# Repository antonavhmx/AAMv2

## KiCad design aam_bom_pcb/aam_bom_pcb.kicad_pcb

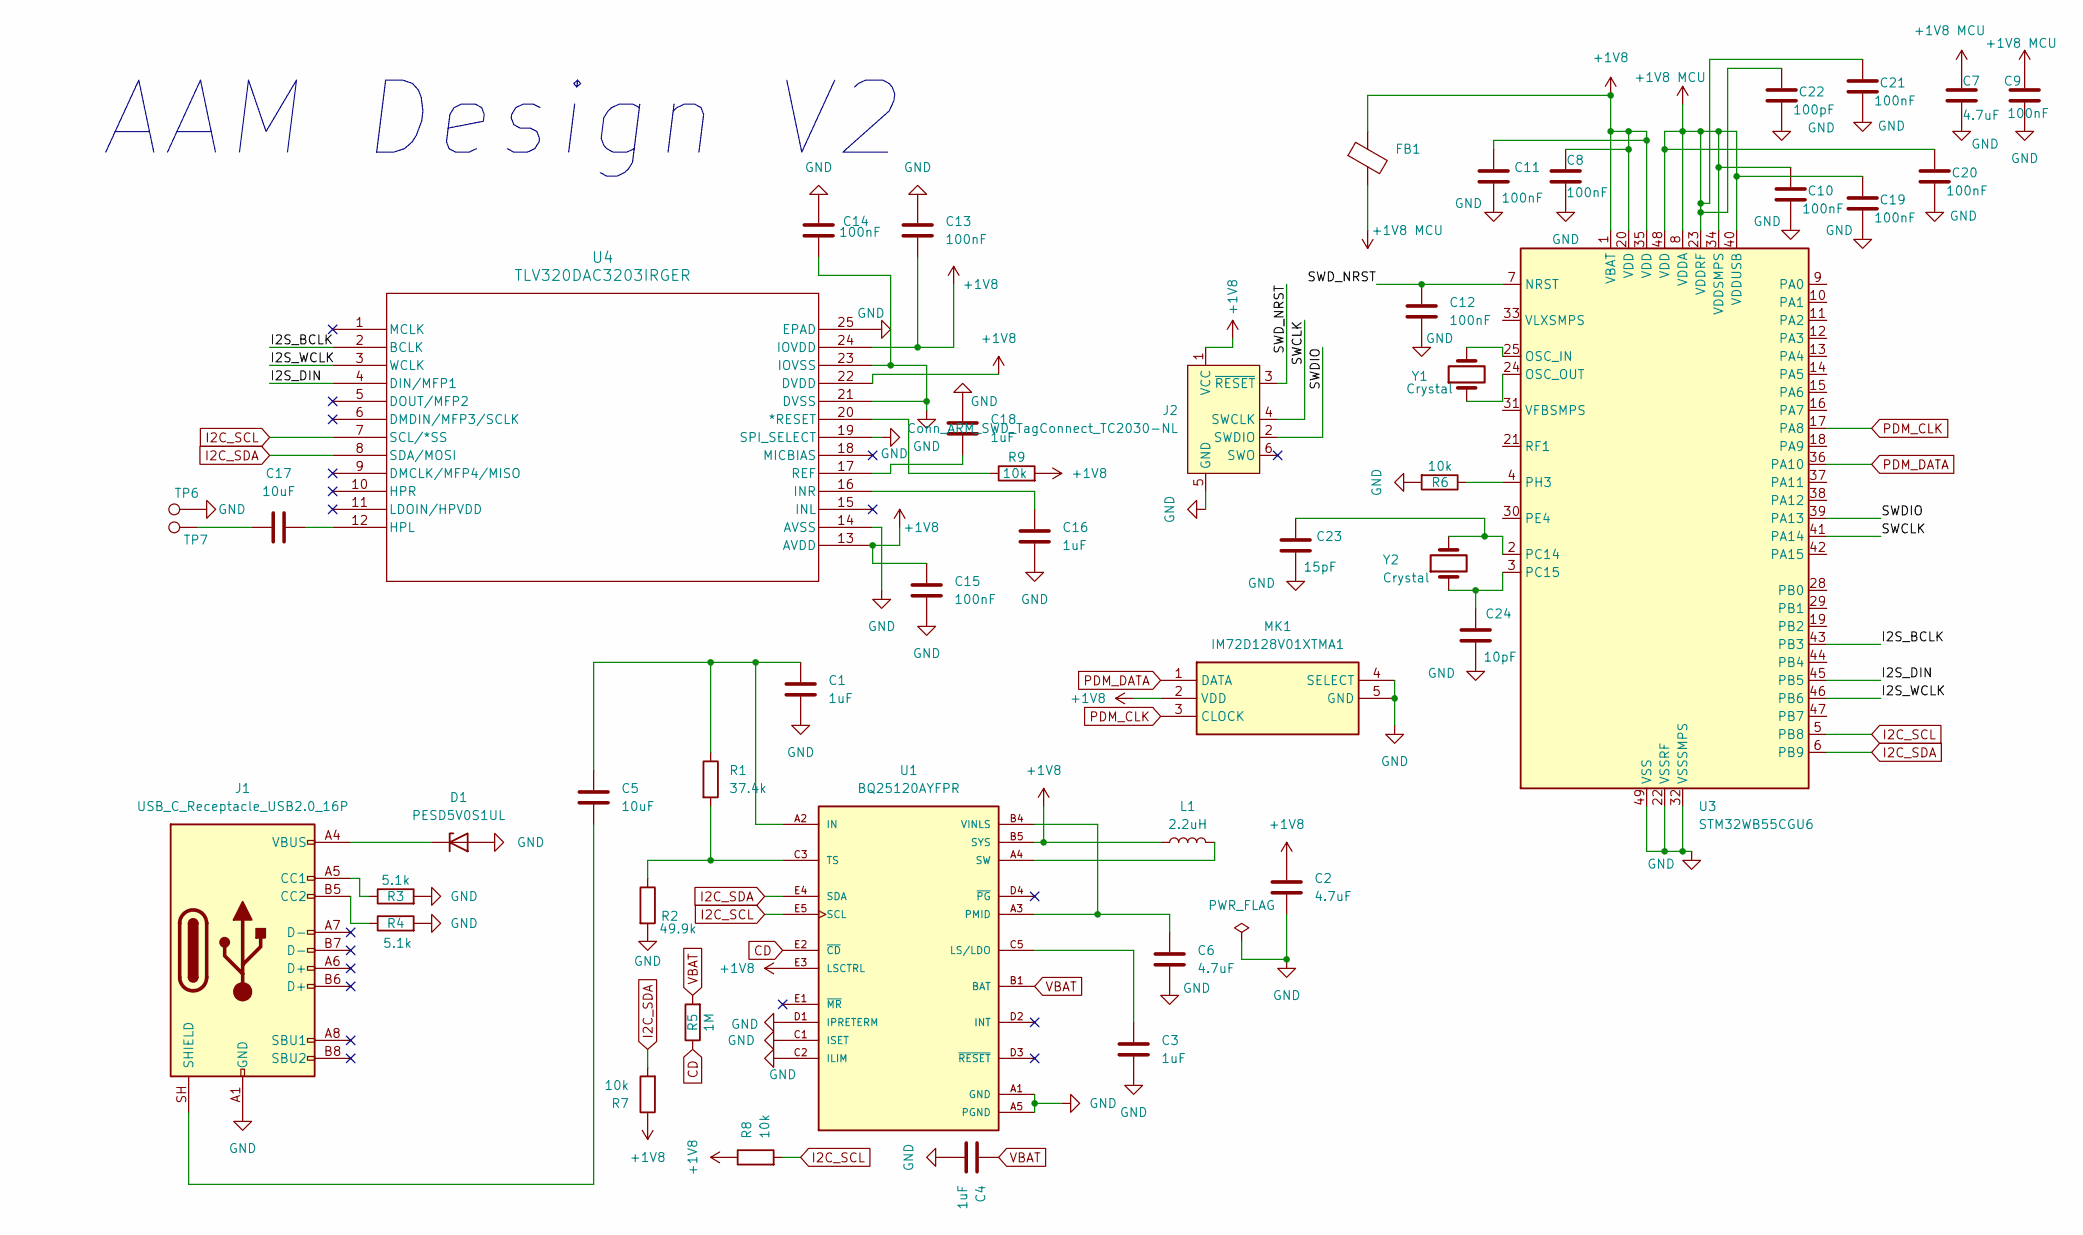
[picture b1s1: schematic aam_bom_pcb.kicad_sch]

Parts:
C1, C3, C4, C16, C18: 1uF; C_0402_1005Metric; LCSC C52923
C2, C6, C7: 4.7uF; C_0402_1005Metric; LCSC C23733
C5, C17: 10uF; C_0402_1005Metric; LCSC C307415
C8, C9, C10, C11, C12, C13, C14, C15, C19, C20, C21: 100nF; C_0402_1005Metric; LCSC C307331
C22: 100pF; C_0402_1005Metric; LCSC C307331
C23: 15pF; C_0402_1005Metric; LCSC C307331
C24: 10pF; C_0402_1005Metric; LCSC C307331
D1: PESD5V0S1UL; D_SOD-882; LCSC C552570
FB1: 600R@100MHz; L_0402_1005Metric; LCSC C76884
J1: USB_C_Receptacle_USB2.0_16P; USB_C_Receptacle_HCTL_HC-TYPE-C-16P-01A; LCSC C2894897
J2: Conn_ARM_SWD_TagConnect_TC2030-NL; Tag-Connect_TC2030-IDC-NL_2x03_P1.27mm_Vertical
L1: 2.2uH; L_1008_2520Metric; LCSC C222790
MK1: IM72D128V01XTMA1; Mouser Part Number 726-IM72D128V01XTMA1
R1: 37.4k; R_0402_1005Metric; LCSC C185422
R2: 49.9k; R_0402_1005Metric; LCSC C137969
R3, R4: 5.1k; R_0402_1005Metric; LCSC C105872
R5: 1M; R_0402_1005Metric; LCSC C138033
R6, R7, R8, R9: 10k; R_0402_1005Metric; LCSC C60490
TP6, TP7: TestPoint; TestPoint_Pad_1.5x1.5mm
U1: BQ25120AYFPR; IC_BQ25120AYFPR; PARTREV A; LCSC C2866577
U3: STM32WB55CGU6; QFN-48-1EP_7x7mm_P0.5mm_EP5.6x5.6mm; LCSC C404023
U4: TLV320DAC3203IRGER; RGE24_2P7X2P7_TEX; LCSC C473906
Y1: Crystal; Crystal_SMD_2016-4Pin_2.0x1.6mm; LCSC C9009
Y2: Crystal; Crystal_SMD_2012-2Pin_2.0x1.2mm; LCSC C32346

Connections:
+1V8: C2.1, C8.1, C11.1, C13.2, C15.1, FB1.1, J2.1 (VCC), L1.1, MK1.2 (VDD), R7.1, R8.1, R9.2, U1.B5 (SYS), U1.E3 (LSCTRL), U3.1 (VBAT), U3.20 (VDD), U3.35 (VDD), U4.13 (AVDD), U4.22 (DVDD), U4.24 (IOVDD)
+1V8 MCU: C7.1, C9.1, C10.1, C19.1, C20.1, C21.1, C22.1, FB1.2, U3.8 (VDDA), U3.23 (VDDRF), U3.34 (VDDSMPS), U3.40 (VDDUSB), U3.48 (VDD)
/I2S_BCLK: U3.43 (PB3), U4.2 (BCLK)
/I2S_DIN: U3.45 (PB5), U4.4 (DIN/MFP1)
/I2S_WCLK: U3.46 (PB6), U4.3 (WCLK)
/SWCLK: J2.4 (SWCLK), U3.41 (PA14)
/SWDIO: J2.2 (SWDIO), U3.39 (PA13)
/SWD_NRST: C12.1, J2.3 (~RESET), U3.7 (NRST)
CD: R5.1, U1.E2 (~CD)
GND: C1.2, C2.2, C3.2, C4.2, C6.2, C7.2, C8.2, C9.2, C10.2, C11.2, C12.2, C13.1, C14.1, C14.2, C15.2, C16.2, C18.1, C19.2, C20.2, C21.2, C22.2, C23.2, C24.2, D1.2 (A), J1.A1 (GND), J1.A12 (GND), J1.B1 (GND), J1.B12 (GND), J2.5 (GND), MK1.4 (SELECT), MK1.5 (GND), R2.2, R3.2, R4.2, R6.2, TP6.1 (1_1), U1.A1 (GND), U1.A5 (PGND), U1.C1 (ISET), U1.C2 (ILIM), U1.D1 (IPRETERM), U1.D5 (GND), U3.22 (VSSRF), U3.32 (VSSSMPS), U3.49 (VSS), U4.14 (AVSS), U4.19 (SPI_SELECT), U4.21 (DVSS), U4.23 (IOVSS), U4.25 (EPAD); also elsewhere on the board
I2C_SCL: R8.2, U1.E5 (SCL), U3.5 (PB8), U4.7 (SCL/*SS)
I2C_SDA: R7.2, U1.E4 (SDA), U3.6 (PB9), U4.8 (SDA/MOSI)
unnamed: C6.1, U1.A3 (PMID), U1.B3 (PMID), U1.B4 (VINLS), U1.C4 (VINLS)
unnamed: C17.1, TP7.1 (1_1)
unnamed: D1.1 (K), J1.A4 (VBUS), J1.A9 (VBUS), J1.B4 (VBUS), J1.B9 (VBUS)
unnamed: J1.A5 (CC1), R3.1
unnamed: J1.B5 (CC2), R4.1
unnamed: C5.2, J1.SH (SHIELD)
unnamed: C1.1, C5.1, R1.1, U1.A2 (IN)
unnamed: C3.1, U1.C5 (LS/LDO)
unnamed: L1.2, U1.A4 (SW)
unnamed: R1.2, R2.1, U1.C3 (TS)
unnamed: U3.25 (OSC_IN), Y1.2
unnamed: U3.24 (OSC_OUT), Y1.1
unnamed: C23.1, U3.2 (PC14), Y2.2
unnamed: C24.1, U3.3 (PC15), Y2.1
unnamed: R6.1, U3.4 (PH3)
unnamed: R9.1, U4.20 (*RESET)
unnamed: C17.2, U4.12 (HPL)
unnamed: C16.1, U4.16 (INR)
unnamed: C18.2, U4.17 (REF)
PDM_CLK: MK1.3 (CLOCK), U3.17 (PA8)
PDM_DATA: MK1.1 (DATA), U3.36 (PA10)
VBAT: C4.1, R5.2, U1.B1 (BAT), U1.B2 (BAT)

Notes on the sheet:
AAM Design V2

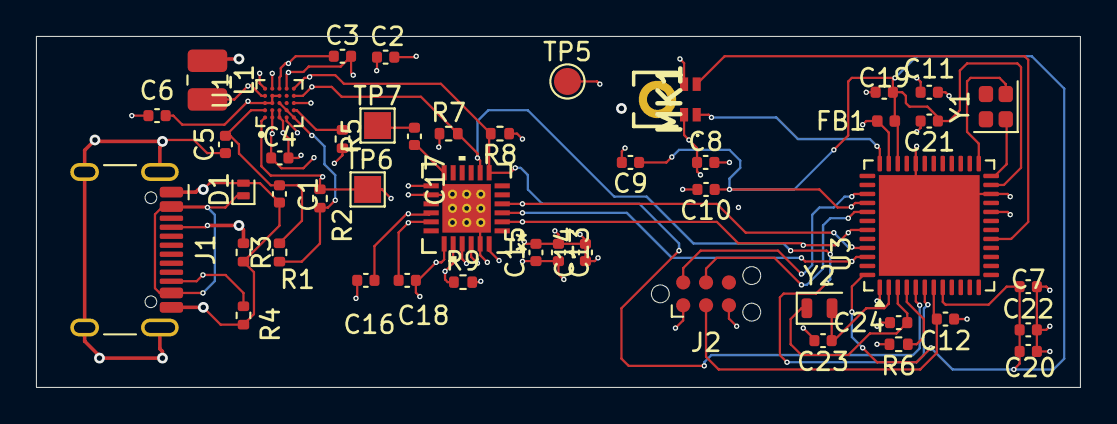
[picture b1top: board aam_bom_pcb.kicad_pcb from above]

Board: 4 copper layers, 58.0 x 19.5 mm, 47 parts (0 on the bottom side), 34 nets.

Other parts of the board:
TP5: TestPoint; TestPoint_Pad_D1.5mm

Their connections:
GND: TP5.1 (1_1); also elsewhere on the board

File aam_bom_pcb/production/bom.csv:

Designator,Footprint,Quantity,Value,LCSC Part #
"C1, C16, C18, C3, C4",402,5,1uF,C52923
"C10, C11, C12, C13, C14, C15, C8, C9",402,8,100nF,C23733
"C17, C5",402,2,10uF,C307415
"C2, C6, C7",402,3,4.7uF,C307331
D1,D_SOD-882,1,PESD5V0S1UL,C552570
FB1,402,1,FerriteBead,C76884
J1,USB_C_Receptacle_HCTL_HC-TYPE-C-16P-01A,1,USB_C_Receptacle_USB2.0_16P,C2894897
L1,1008,1,2.2uH,C222790
MK1,IM72D128V01XTMA1,1,IM72D128V01XTMA1,C5119248
R1,402,1,37k,C185422
R2,402,1,50k,C137969
"R3, R4",402,2,5.1k,C105872
R5,402,1,1M,C138033
"R6, R7, R8, R9",402,4,10k,C60490
TP5,TestPoint_Pad_D1.5mm,1,TestPoint,
"TP6, TP7",TestPoint_Pad_1.5x1.5mm,2,TestPoint,
U1,IC_BQ25120AYFPR,1,BQ25120AYFPR,C2866577
U3,ST-SiP-LGA-86-11x7.3mm,1,STM32WB5MMG,C5184586
U4,RGE24_2P7X2P7_TEX,1,TLV320DAC3203IRGER,C473906
